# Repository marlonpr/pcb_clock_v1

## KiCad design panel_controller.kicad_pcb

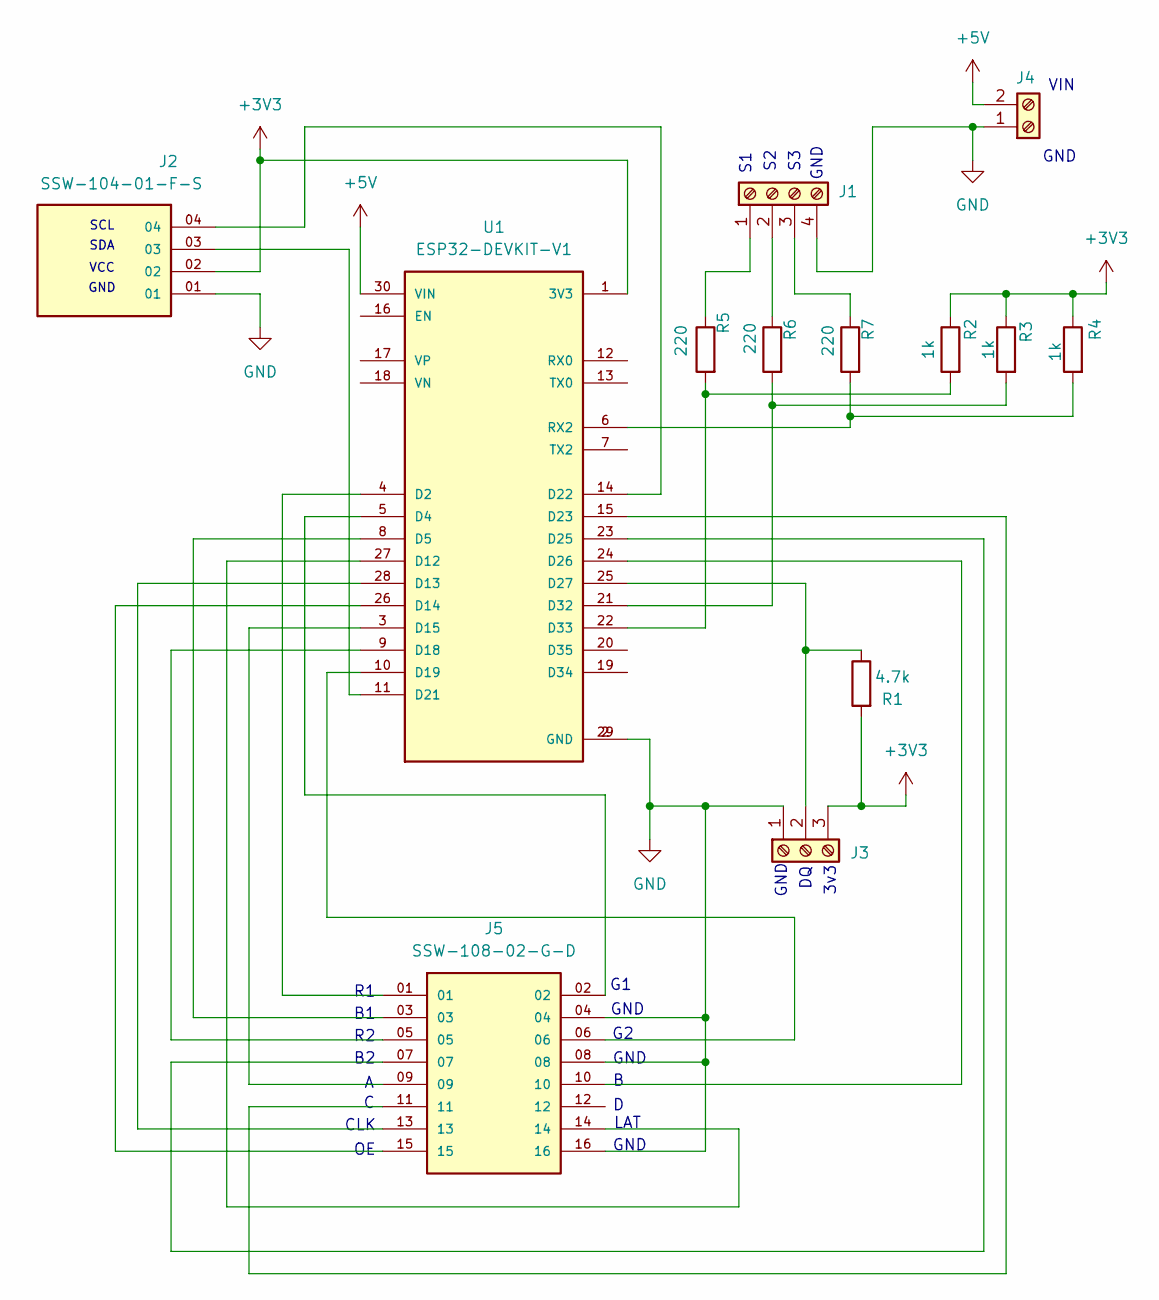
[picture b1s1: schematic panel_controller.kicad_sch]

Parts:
J1: Screw_Terminal_01x04; TerminalBlock_Altech_AK300-4_P5.00mm
J2: SSW-104-01-F-S; SAMTEC_SSW-104-01-F-S-RTC; PARTREV R
J3: Screw_Terminal_01x03; TerminalBlock_Altech_AK300-3_P5.00mm
J4: Screw_Terminal_01x02; TerminalBlock_Altech_AK300-2_P5.00mm
J5: SSW-108-02-G-D; SAMTEC_SSW-108-02-G-D
R1: 4.7k; R_Axial_DIN0204_L3.6mm_D1.6mm_P5.08mm_Horizontal
R2, R3, R4: 1k; R_Axial_DIN0204_L3.6mm_D1.6mm_P5.08mm_Horizontal
R5, R6, R7: 220; R_Axial_DIN0204_L3.6mm_D1.6mm_P5.08mm_Horizontal
U1: ESP32-DEVKIT-V1; MODULE_ESP32_DEVKIT_V1; PARTREV N/A

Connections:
+3V3: J2.02, J3.3, R1.2, R2.1, R3.1, R4.1, U1.1 (3V3)
+5V: J4.2, U1.30 (VIN)
GND: J1.4, J2.01, J3.1, J4.1, J5.04, J5.08, J5.16, U1.2 (GND), U1.29 (GND)
unnamed: J1.1, R5.1
unnamed: J1.2, R6.1
unnamed: J1.3, R7.1
unnamed: J3.2, R1.1, U1.25 (D27)
unnamed: J5.01, U1.4 (D2)
unnamed: J5.02, U1.5 (D4)
unnamed: J5.03, U1.8 (D5)
unnamed: J5.14, U1.27 (D12)
unnamed: J5.13, U1.28 (D13)
unnamed: J5.15, U1.26 (D14)
unnamed: J5.09, U1.3 (D15)
unnamed: J5.05, U1.9 (D18)
unnamed: J5.06, U1.10 (D19)
unnamed: J2.03, U1.11 (D21)
unnamed: J2.04, U1.14 (D22)
unnamed: J5.11, U1.15 (D23)
unnamed: J5.07, U1.23 (D25)
unnamed: J5.10, U1.24 (D26)
unnamed: R3.2, R6.2, U1.21 (D32)
unnamed: R2.2, R5.2, U1.22 (D33)
unnamed: R4.2, R7.2, U1.6 (RX2)

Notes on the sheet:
GND
VCC
SDA
SCL
3v3
CLK
VIN
LAT

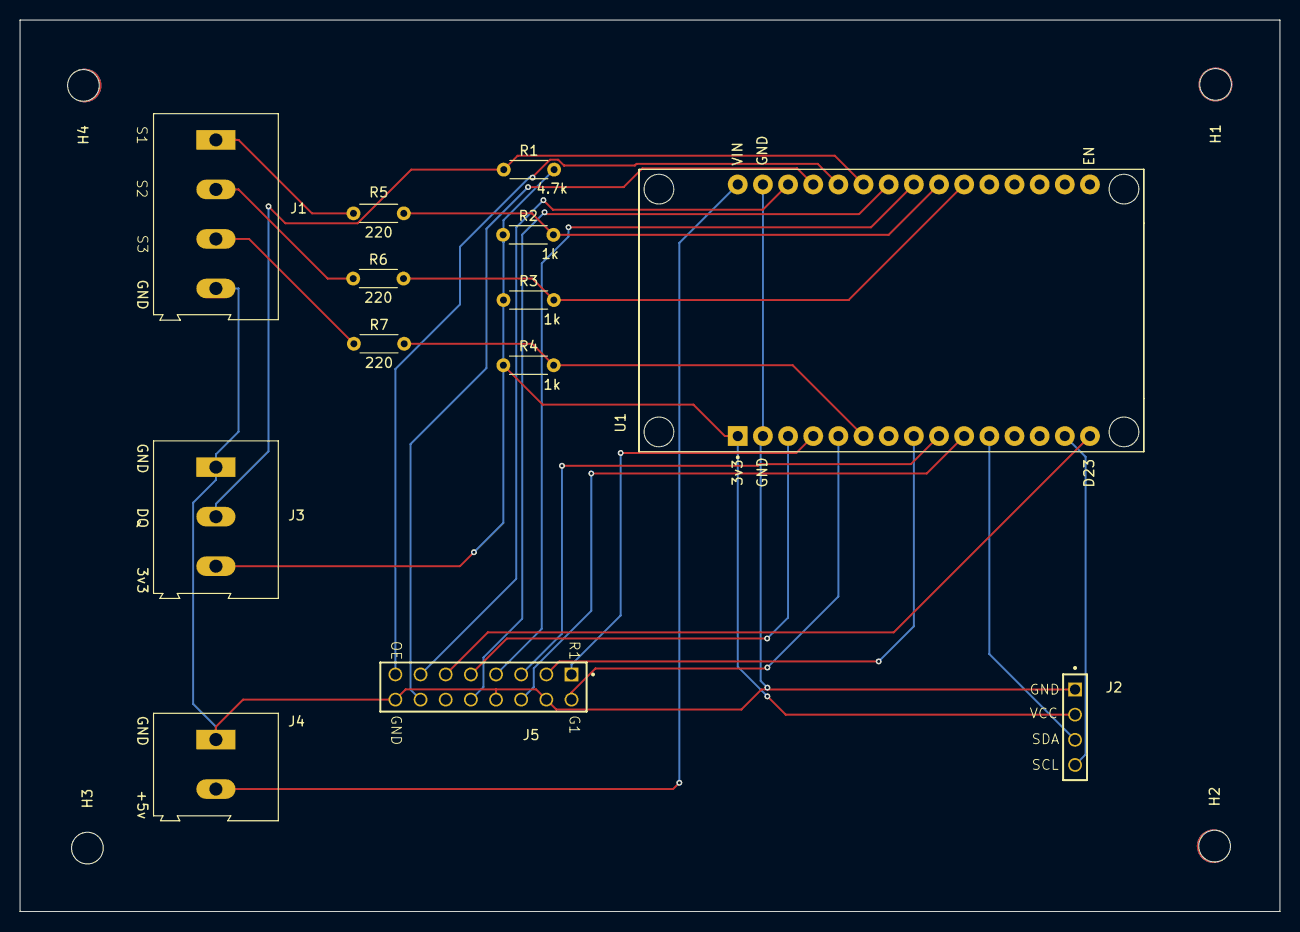
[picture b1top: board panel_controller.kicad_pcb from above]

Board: 2 copper layers, 127.2 x 90.0 mm, 17 parts (0 on the bottom side), 24 nets.

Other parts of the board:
H1, H2, H3, H4: MountingHole_3.2mm_M3

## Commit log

2025-08-26 pcb clock v1.0
2025-08-27 pcb clock v1.1
2025-10-01 pcb clock v1.2
2025-10-02 pcb clock v1.3
2025-10-02 pcb clock v1.4
2025-10-06 pcb clock v1.5
2025-10-14 pcb clock v1.6
2025-12-09 pcb clock v1.7 rerouting for proper track width
2026-01-12 pcb clock v1.8
